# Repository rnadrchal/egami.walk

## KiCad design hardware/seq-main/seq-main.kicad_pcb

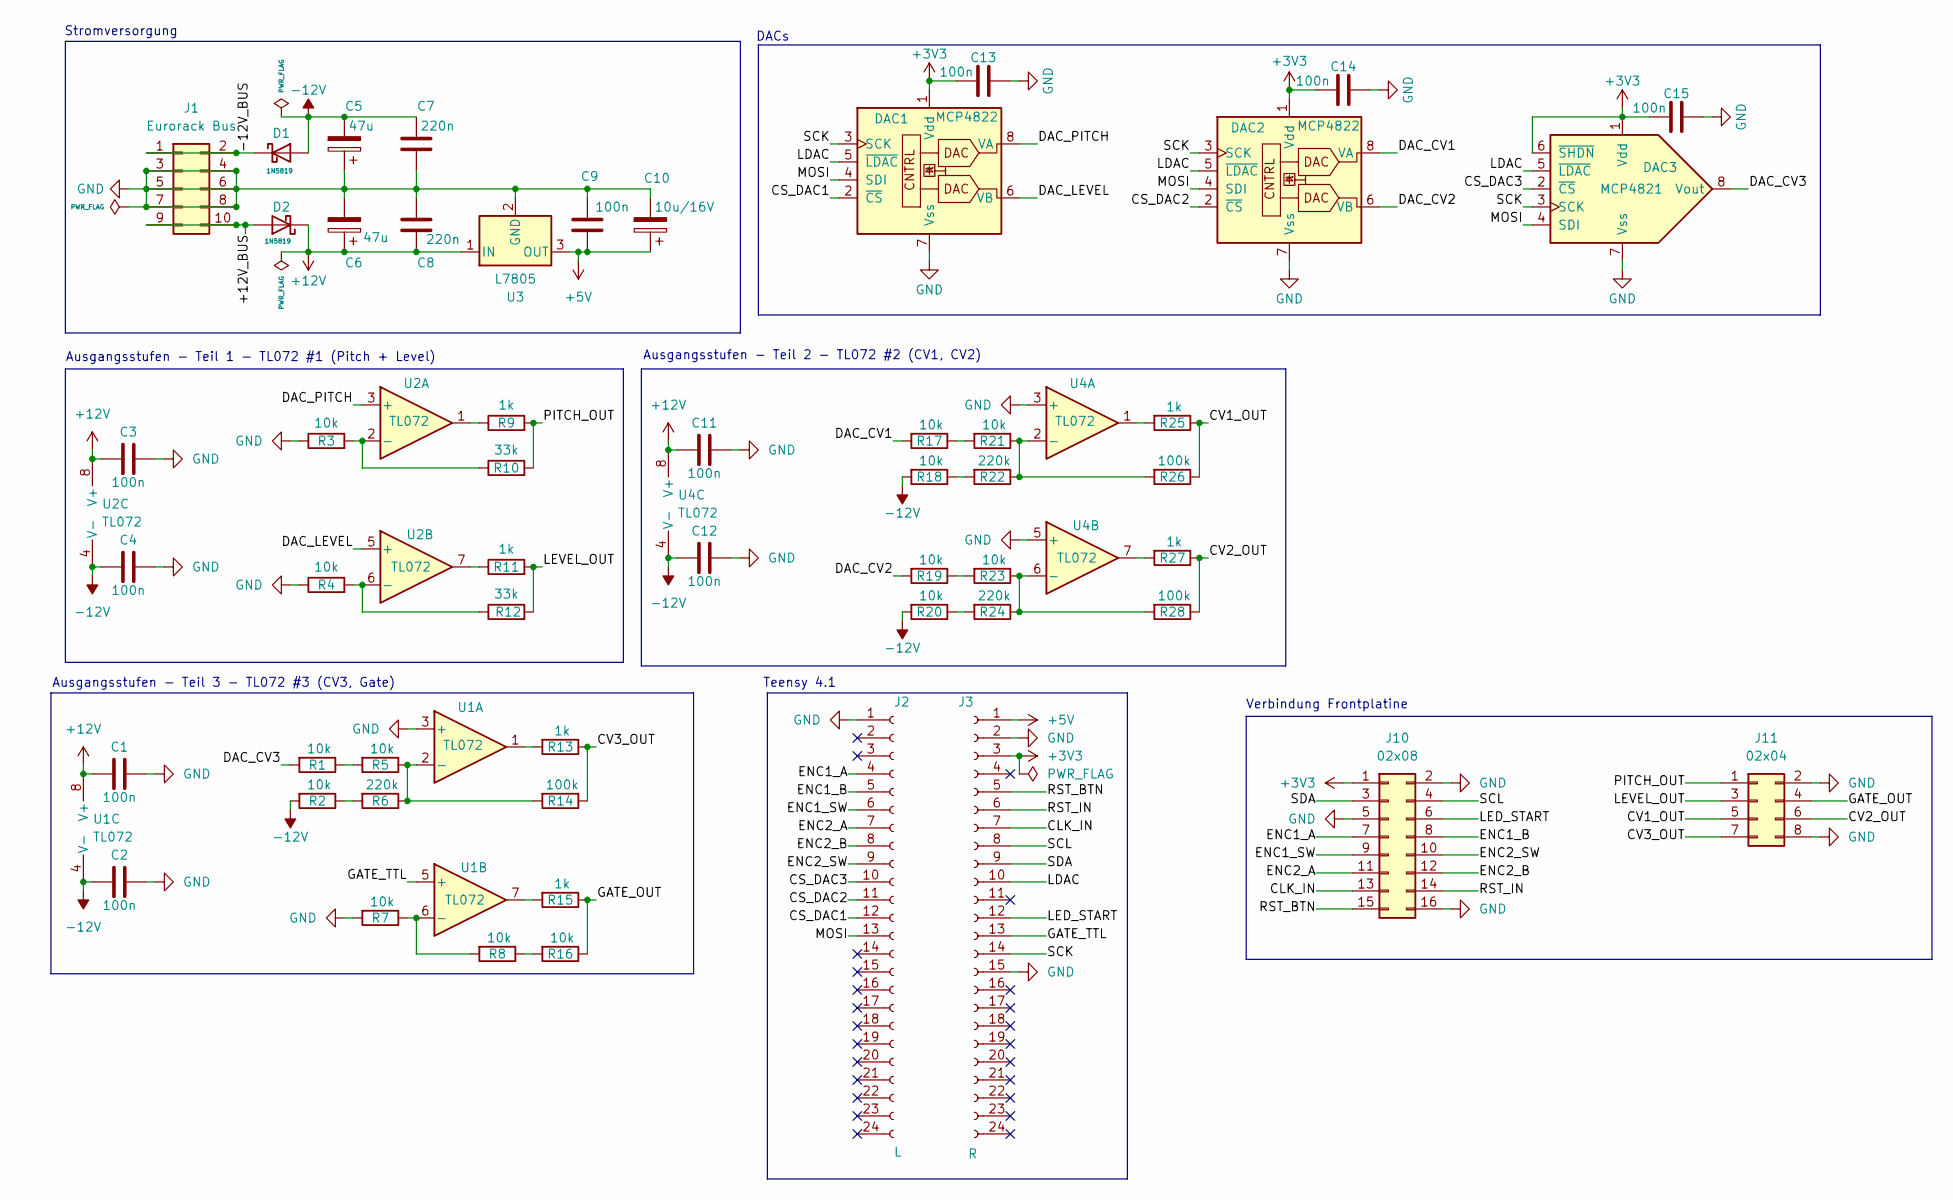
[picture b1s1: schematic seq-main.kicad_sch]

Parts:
C1, C2, C3, C4, C9, C11, C12, C13, C14, C15: 100n; C_Disc_D5.0mm_W2.5mm_P5.00mm
C5, C6: 47u; CP_Radial_D5.0mm_P2.50mm
C7, C8: 220n; C_Disc_D5.0mm_W2.5mm_P5.00mm
C10: 10u/16V; CP_Radial_D4.0mm_P2.00mm
D1, D2: 1N5819; D_DO-41_SOD81_P10.16mm_Horizontal
DAC1, DAC2: MCP4822; DIP-8_W7.62mm_Socket
DAC3: MCP4821; DIP-8_W7.62mm_Socket
J1: Eurorack Bus; IDC-Header_2x05_P2.54mm_Vertical
J2: L; PinSocket_1x24_P2.54mm_Vertical
J3: R; PinSocket_1x24_P2.54mm_Vertical
J10: 02x08; PinSocket_2x08_P2.54mm_Vertical
J11: 02x04; PinSocket_2x04_P2.54mm_Vertical
R1, R2, R3, R4, R5, R7, R8, R16, R17, R18, R19, R20, R21, R23: 10k; R_Axial_DIN0207_L6.3mm_D2.5mm_P10.16mm_Horizontal
R6, R22, R24: 220k; R_Axial_DIN0207_L6.3mm_D2.5mm_P10.16mm_Horizontal
R9, R11, R13, R15, R25, R27: 1k; R_Axial_DIN0207_L6.3mm_D2.5mm_P10.16mm_Horizontal
R10, R12: 33k; R_Axial_DIN0207_L6.3mm_D2.5mm_P10.16mm_Horizontal
R14, R26, R28: 100k; R_Axial_DIN0207_L6.3mm_D2.5mm_P10.16mm_Horizontal
U1, U2, U4: TL072; DIP-8_W7.62mm_Socket
U3: L7805; TO-220-3_Horizontal_TabUp

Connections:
+3V3: C13.1, C14.1, C15.1, DAC1.1 (Vdd), DAC2.1 (Vdd), DAC3.1 (Vdd), DAC3.6 (~SHDN), J3.3, J10.1
+5V: C9.2, C10.1, J3.1, U3.3 (OUT)
+12V: C1.1, C3.1, C6.1, C8.2, C11.1, D2.1 (K), U1.8 (V+), U2.8 (V+), U3.1 (IN), U4.8 (V+)
-12V: C2.1, C4.1, C5.2, C7.1, C12.1, D1.2 (A), R2.2, R18.2, R20.2, U1.4 (V-), U2.4 (V-), U4.4 (V-)
/+12V_BUS: D2.2 (A), J1.9, J1.10
/-12V_BUS: D1.1 (K), J1.1, J1.2
/CLK_IN: J3.7, J10.13
/CS_DAC1: DAC1.2 (~CS), J2.12
/CS_DAC2: DAC2.2 (~CS), J2.11
/CS_DAC3: DAC3.2 (~CS), J2.10
/CV1_OUT: J11.5, R25.1, R26.1
/CV2_OUT: J11.6, R27.1, R28.1
/CV3_OUT: J11.7, R13.1, R14.1
/DAC_CV1: DAC2.8 (VA), R17.2
/DAC_CV2: DAC2.6 (VB), R19.2
/DAC_CV3: DAC3.8 (Vout), R1.2
/DAC_LEVEL: DAC1.6 (VB), U2.5 (+)
/DAC_PITCH: DAC1.8 (VA), U2.3 (+)
/ENC1_A: J2.4, J10.7
/ENC1_B: J2.5, J10.8
/ENC1_SW: J2.6, J10.9
/ENC2_A: J2.7, J10.11
/ENC2_B: J2.8, J10.12
/ENC2_SW: J2.9, J10.10
/GATE_OUT: J11.4, R15.1, R16.1
/GATE_TTL: J3.13, U1.5 (+)
/LDAC: DAC1.5 (~LDAC), DAC2.5 (~LDAC), DAC3.5 (~LDAC), J3.10
/LED_START: J3.12, J10.6
/LEVEL_OUT: J11.3, R11.2, R12.2
/MOSI: DAC1.4 (SDI), DAC2.4 (SDI), DAC3.4 (SDI), J2.13
/PITCH_OUT: J11.1, R9.2, R10.2
/RST_BTN: J3.5, J10.15
/RST_IN: J3.6, J10.14
/SCK: DAC1.3 (SCK), DAC2.3 (SCK), DAC3.3 (SCK), J3.14
/SCL: J3.8, J10.4
/SDA: J3.9, J10.3
GND: C1.2, C2.2, C3.2, C4.2, C5.1, C6.2, C7.2, C8.1, C9.1, C10.2, C11.2, C12.2, C13.2, C14.2, C15.2, DAC1.7 (Vss), DAC2.7 (Vss), DAC3.7 (Vss), J1.3, J1.4, J1.5, J1.6, J1.7, J1.8, J2.1, J3.2, J3.15, J10.2, J10.5, J10.16, J11.2, J11.8, R3.1, R4.1, R7.2, U1.3 (+), U3.2 (GND), U4.3 (+), U4.5 (+)
unnamed: R1.1, R5.2
unnamed: R2.1, R6.2
unnamed: R9.1, U2.1
unnamed: R11.1, U2.7
unnamed: R13.2, U1.1
unnamed: R15.2, U1.7
unnamed: R8.1, R16.2
unnamed: R17.1, R21.2
unnamed: R18.1, R22.2
unnamed: R19.1, R23.2
unnamed: R20.1, R24.2
unnamed: R25.2, U4.1
unnamed: R27.2, U4.7
unnamed: R5.1, R6.1, R14.2, U1.2 (-)
unnamed: R7.1, R8.2, U1.6 (-)
unnamed: R3.2, R10.1, U2.2 (-)
unnamed: R4.2, R12.1, U2.6 (-)
unnamed: R21.1, R22.1, R26.2, U4.2 (-)
unnamed: R23.1, R24.1, R28.2, U4.6 (-)

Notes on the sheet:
Verbindung Frontplatine
Stromversorgung
Teensy 4.1
Ausgangsstufen - Teil 1 - TL072 #1 (Pitch + Level)
Ausgangsstufen - Teil 2 - TL072 #2 (CV1, CV2)
DACs
Ausgangsstufen - Teil 3 - TL072 #3 (CV3, Gate)

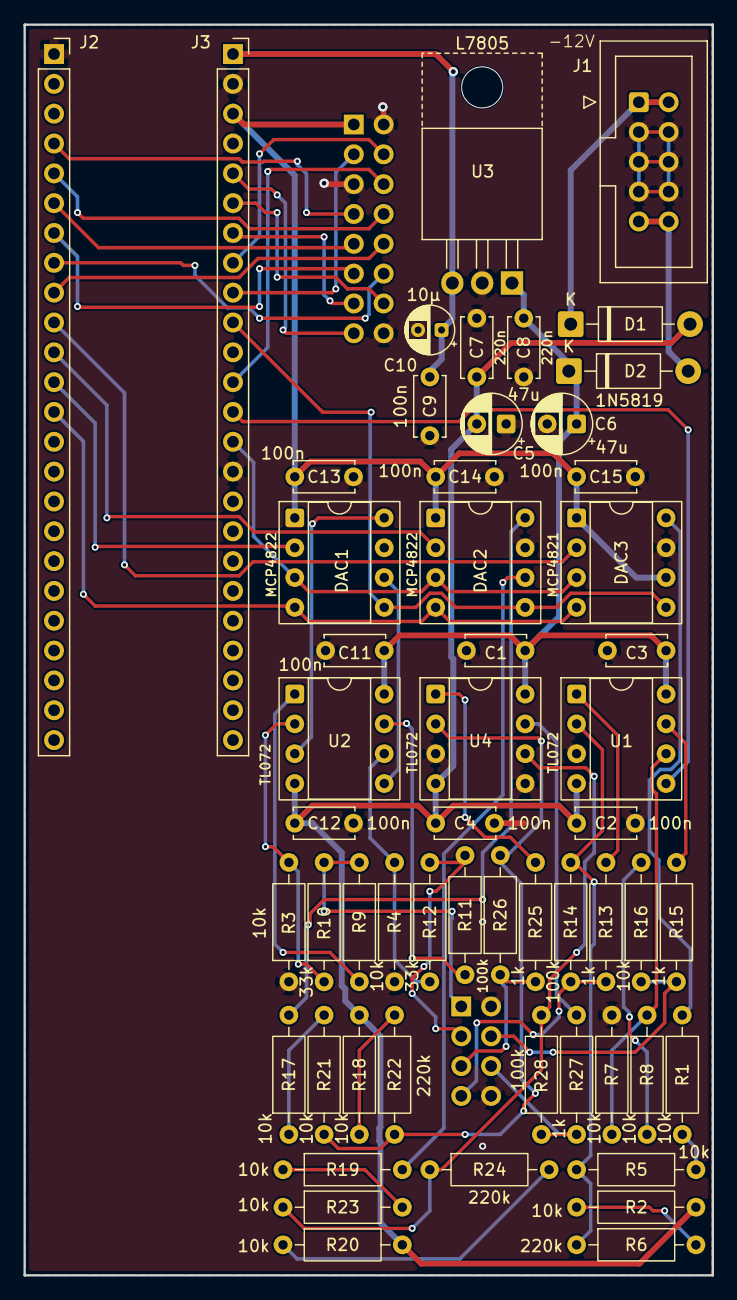
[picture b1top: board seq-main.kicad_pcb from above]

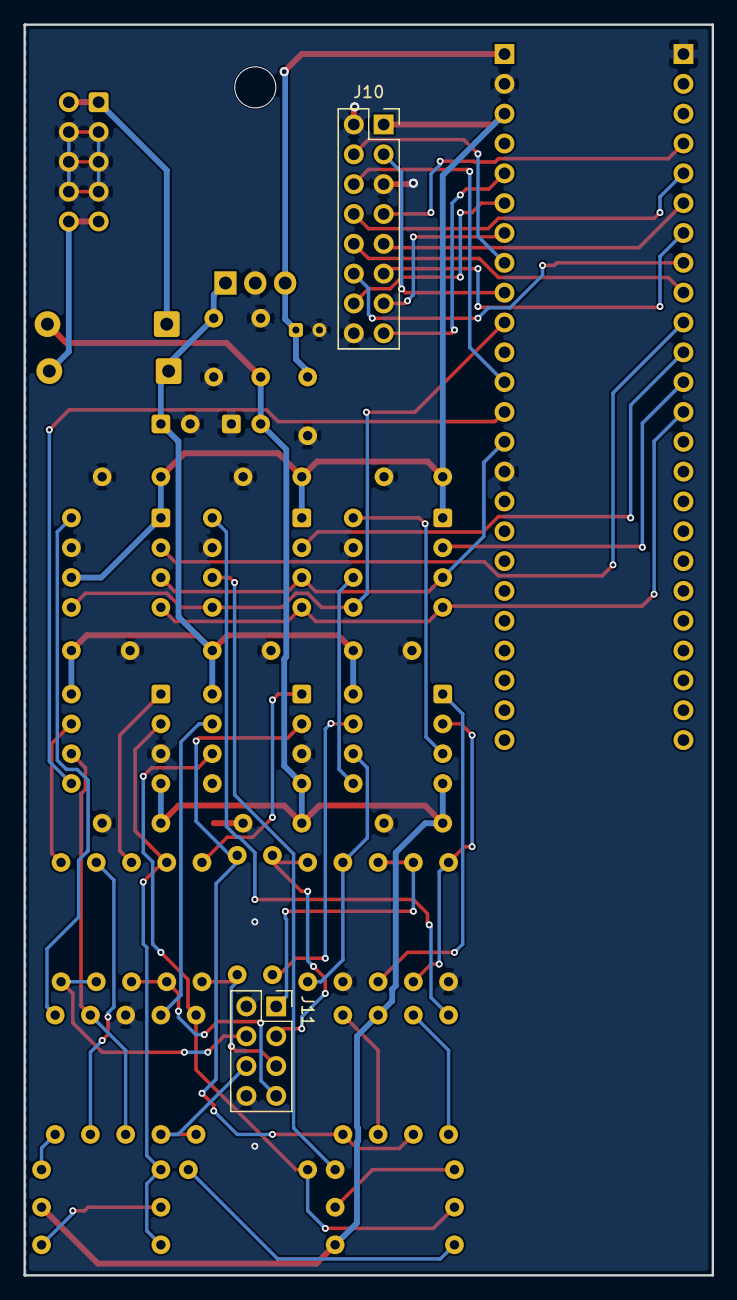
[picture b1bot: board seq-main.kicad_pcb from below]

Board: 2 copper layers, 58.6 x 106.5 mm, 57 parts (2 on the bottom side), 56 nets.

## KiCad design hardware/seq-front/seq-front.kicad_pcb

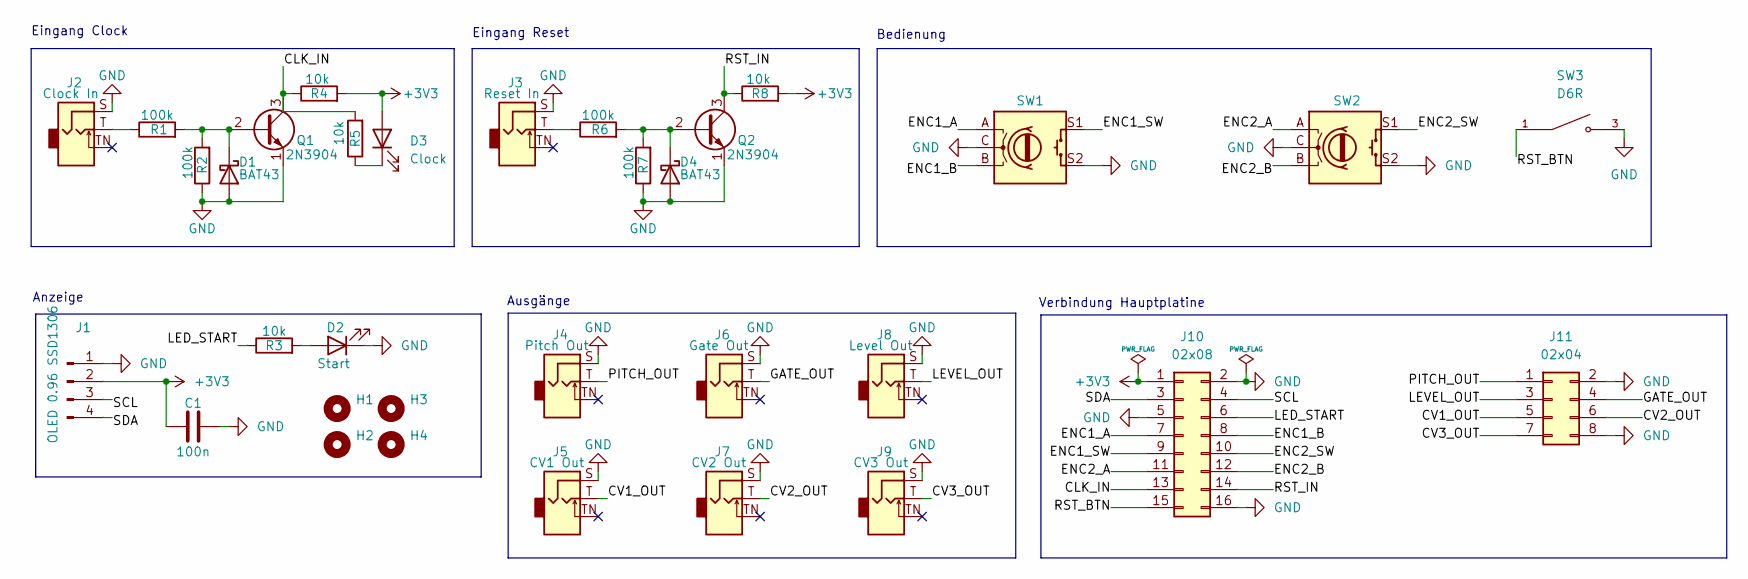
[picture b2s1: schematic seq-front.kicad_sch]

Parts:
C1: 100n; C_Disc_D5.0mm_W2.5mm_P5.00mm
D1, D4: BAT43; D_DO-35_SOD27_P7.62mm_Horizontal
D2: Start; LED_D3.0mm
D3: Clock; LED_D3.0mm
H1, H2, H3, H4: MountingHole_2.7mm_M2.5
J1: OLED 0.96 SSD1306; PinHeader_1x04_P2.54mm_Vertical
J2: Clock In; Jack_3.5mm_QingPu_WQP-PJ398SM_Vertical_CircularHoles
J3: Reset In; Jack_3.5mm_QingPu_WQP-PJ398SM_Vertical_CircularHoles
J4: Pitch Out; Jack_3.5mm_QingPu_WQP-PJ398SM_Vertical_CircularHoles
J5: CV1 Out; Jack_3.5mm_QingPu_WQP-PJ398SM_Vertical_CircularHoles
J6: Gate Out; Jack_3.5mm_QingPu_WQP-PJ398SM_Vertical_CircularHoles
J7: CV2 Out; Jack_3.5mm_QingPu_WQP-PJ398SM_Vertical_CircularHoles
J8: Level Out; Jack_3.5mm_QingPu_WQP-PJ398SM_Vertical_CircularHoles
J9: CV3 Out; Jack_3.5mm_QingPu_WQP-PJ398SM_Vertical_CircularHoles
J10: 02x08; PinHeader_2x08_P2.54mm_Vertical
J11: 02x04; PinHeader_2x04_P2.54mm_Vertical
Q1, Q2: 2N3904; TO-92_Inline_Wide
R1, R2, R6, R7: 100k; R_Axial_DIN0207_L6.3mm_D2.5mm_P10.16mm_Horizontal
R3, R4, R5, R8: 10k; R_Axial_DIN0207_L6.3mm_D2.5mm_P10.16mm_Horizontal
SW1, SW2: RotaryEncoder_Alps_EC11E-Switch_Vertical_H20mm_CircularMoun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
SW3: D6R; SW_D6R90_F1_LFS; PARTREV N/A

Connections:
+3V3: C1.1, D3.2 (A), J1.2, J10.1, R4.2, R8.2
/CLK_IN: J10.13, Q1.3 (C), R4.1, R5.2
/CV1_OUT: J5.T, J11.5
/CV2_OUT: J7.T, J11.6
/CV3_OUT: J9.T, J11.7
/ENC1_A: J10.7, SW1.A
/ENC1_B: J10.8, SW1.B
/ENC1_SW: J10.9, SW1.S1
/ENC2_A: J10.11, SW2.A
/ENC2_B: J10.12, SW2.B
/ENC2_SW: J10.10, SW2.S1
/GATE_OUT: J6.T, J11.4
/LED_START: J10.6, R3.1
/LEVEL_OUT: J8.T, J11.3
/PITCH_OUT: J4.T, J11.1
/RST_BTN: J10.15, SW3.1, SW3.2
/RST_IN: J10.14, Q2.3 (C), R8.1
/SCL: J1.3, J10.4
/SDA: J1.4, J10.3
GND: C1.2, D1.2 (A), D2.1 (K), D4.2 (A), J1.1, J2.S, J3.S, J4.S, J5.S, J6.S, J7.S, J8.S, J9.S, J10.2, J10.5, J10.16, J11.2, J11.8, Q1.1 (E), Q2.1 (E), R2.1, R7.1, SW1.C, SW1.S2, SW2.C, SW2.S2, SW3.3, SW3.4
unnamed: D1.1 (K), Q1.2 (B), R1.2, R2.2
unnamed: D2.2 (A), R3.2
unnamed: D3.1 (K), R5.1
unnamed: D4.1 (K), Q2.2 (B), R6.2, R7.2
unnamed: J2.T, R1.1
unnamed: J3.T, R6.1

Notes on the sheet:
Anzeige
Bedienung
Verbindung Hauptplatine
Eingang Clock
Eingang Reset
Ausgänge

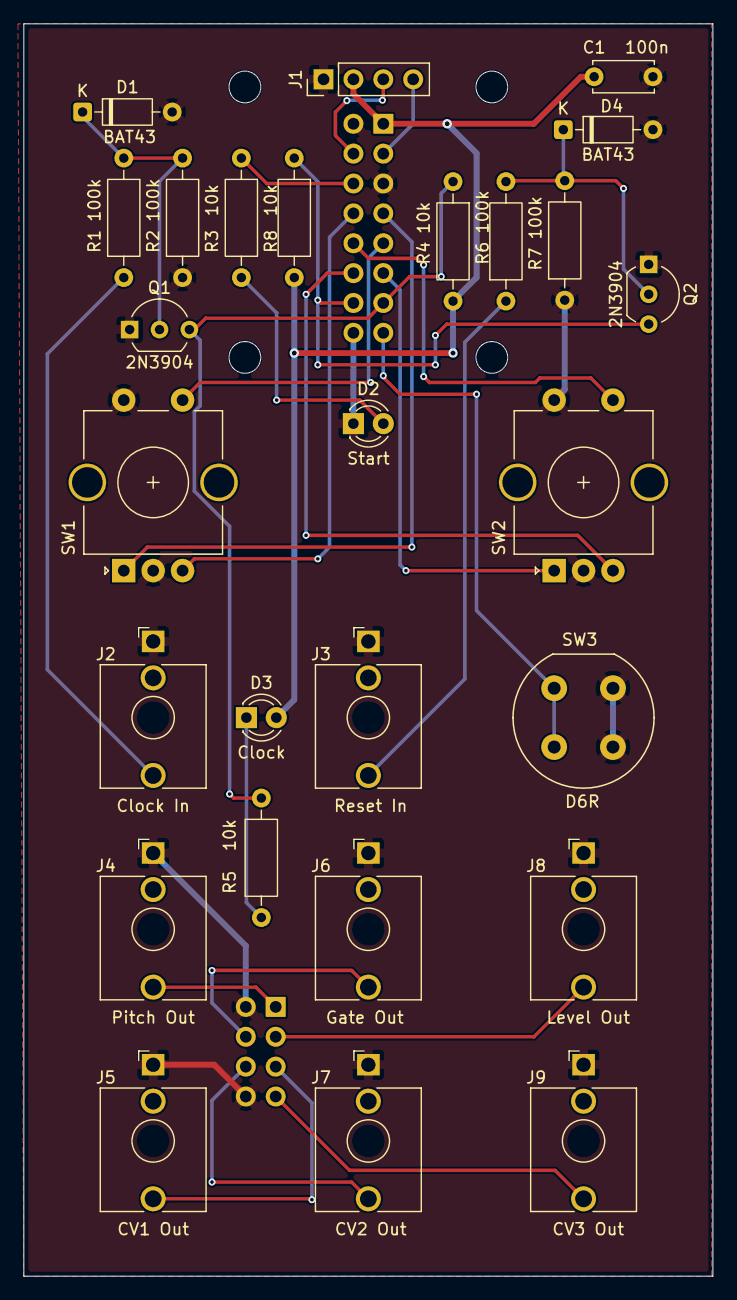
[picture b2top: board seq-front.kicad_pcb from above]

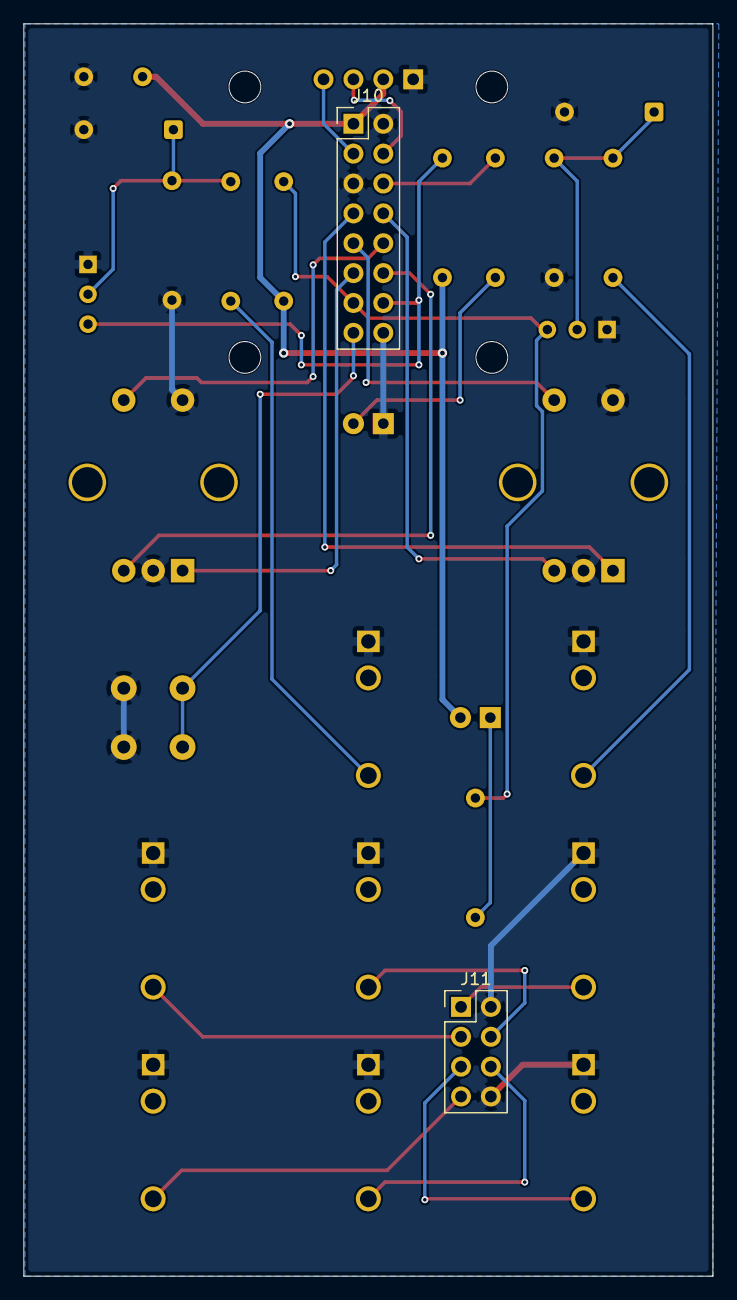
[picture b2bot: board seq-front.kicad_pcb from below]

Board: 2 copper layers, 58.6 x 106.5 mm, 33 parts (2 on the bottom side), 26 nets.

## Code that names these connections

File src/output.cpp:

#include "output.h"
#include <SPI.h>

const uint8_t PIN_CS_DAC1 = 10;
const uint8_t PIN_CS_DAC2 = 9;
const uint8_t PIN_CS_DAC3 = 8;
const uint8_t PIN_LDAC    = 17;

static const SPISettings DAC_SPI(20000000, MSBFIRST, SPI_MODE0);   // MCP482x: max. 20 MHz

// Steuerbits MCP482x: Bit 15 = Kanal (0 = A, 1 = B), Bit 13 = Verstaerkung 1x, Bit 12 = aktiv
const uint16_t CH_A = 0x0000;
const uint16_t CH_B = 0x8000;
const uint16_t GAIN_1X_ACTIVE = 0x3000;

// --- Umrechnung ---------------------------------------------------
// Ausgangsstufe Pitch / Level: nicht-invertierend, Verstaerkung 1 + Rf / Rg
const float RF_PITCH_LEVEL = 33000.0f;   // Steckbrett: 33 kOhm (Plan: 30 kOhm)
const float RG_PITCH_LEVEL = 10000.0f;
const float GAIN_PL        = 1.0f + RF_PITCH_LEVEL / RG_PITCH_LEVEL;   // 4,3

const float CODES_PER_VOLT = 4096.0f / 2.048f;   // 2000 Codes pro Volt am DAC

static uint16_t voltsToCode(float vOut, float gain) {
  int32_t code = lroundf(vOut / gain * CODES_PER_VOLT);
  return (uint16_t)constrain(code, 0, 4095);
}

// Pitch: 1 V/Okt am Ausgang, 0 V = C0
uint16_t pitchToCode(uint8_t pitch) {
  return voltsToCode(pitch / 12.0f, GAIN_PL);
}

// Level 0–100 -> 0–8 V am Ausgang
static uint16_t levelToCode(uint8_t level) {
  return voltsToCode(level * 0.08f, GAIN_PL);
}

// CV −50…+50 (Zehntel-Volt). Ausgangsstufe invertierend mit Offset aus −12 V:
//   Vout = (Rf / Roff) · 12 V − (Rf / Rin) · Vdac   ->   Vdac = (Offset − Vout) / (Rf / Rin)
// Aus den Bauteilen gerechnet (Plan):
//   CV_GAIN   = Rf / Rin              = 100 k / 20 k            = 5,0
//   CV_OFFSET = Rf / Roff · |−12 V|   = 100 k / 240 k · 12 V    = 5,0 V
// Steckbrett gemessen (−12-V-Schiene = −11,74 V, Rin 20 k, Roff 230 k = 220 k + 10 k):
//   DAC 0 V -> +4,98 V, Verstaerkung aus erster Messung (Rin unveraendert) 5,035
const float CV_GAIN     = 5.035f;
const float CV_OFFSET   = 4.980f;
// -> spaeter durch Kalibrierung (Nullpunkt + Steigung pro CV-Ausgang) ersetzen

static uint16_t cvToCode(int8_t cv) {
  float vOut = cv * 0.1f;
  float vDac = (CV_OFFSET - vOut) / CV_GAIN;
  int32_t code = lroundf(vDac * CODES_PER_VOLT);
  return (uint16_t)constrain(code, 0, 4095);
}

// --- SPI ------------------------------------------------------------
static void dacWrite(uint8_t csPin, uint16_t channel, uint16_t code) {
  uint16_t word = channel | GAIN_1X_ACTIVE | (code & 0x0FFF);
  SPI.beginTransaction(DAC_SPI);
  digitalWriteFast(csPin, LOW);
  SPI.transfer16(word);
  digitalWriteFast(csPin, HIGH);
  SPI.endTransaction();
}

static void ldacPulse() {
  digitalWriteFast(PIN_LDAC, LOW);    // mind. 100 ns
  delayNanoseconds(200);
  digitalWriteFast(PIN_LDAC, HIGH);
}

// --- Oeffentlich ----------------------------------------------------
void outBegin() {
  pinMode(PIN_CS_DAC1, OUTPUT); digitalWriteFast(PIN_CS_DAC1, HIGH);
  pinMode(PIN_CS_DAC2, OUTPUT); digitalWriteFast(PIN_CS_DAC2, HIGH);
  pinMode(PIN_CS_DAC3, OUTPUT); digitalWriteFast(PIN_CS_DAC3, HIGH);
  pinMode(PIN_LDAC,    OUTPUT); digitalWriteFast(PIN_LDAC,    HIGH);
  SPI.begin();

  int8_t zero[3] = { 0, 0, 0 };
  outStep(0, 0, zero);
}

void outStep(uint16_t pitchCode, uint8_t level, const int8_t cv[3]) {
  dacWrite(PIN_CS_DAC1, CH_A, pitchCode);
  dacWrite(PIN_CS_DAC1, CH_B, levelToCode(level));
  dacWrite(PIN_CS_DAC2, CH_A, cvToCode(cv[0]));
  dacWrite(PIN_CS_DAC2, CH_B, cvToCode(cv[1]));
  dacWrite(PIN_CS_DAC3, CH_A, cvToCode(cv[2]));   // MCP4821: Bit 15 muss 0 sein
  ldacPulse();
}

void outPitchCode(uint16_t code) {
  dacWrite(PIN_CS_DAC1, CH_A, code);
  ldacPulse();
}

void outLevel(uint8_t level) {
  dacWrite(PIN_CS_DAC1, CH_B, levelToCode(level));
  ldacPulse();
}
